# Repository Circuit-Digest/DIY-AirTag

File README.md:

# DIY AirTag: Never Lose Your Keys Again!

We all know that there is nothing more infuriating than forgetting where we placed something important or misplaced things. Losing your keys, wallet, or other valuable items can be a frustrating experience. Apple recognised this common problem and introduced the AirTag, a small, Bluetooth-enabled device that helps you keep track of your belongings. By attaching an AirTag to your items, you can easily locate them using the "Find My" app on your iPhone. The AirTag sends a secure Bluetooth signal that nearby devices in the Find My network can detect, allowing you to see the item's location on a map. Inspired by the functionality and usefulness of Apple's AirTag, we created a DIY solution that brings similar benefits with a personal touch. This project involves creating your own Bluetooth Low Energy (BLE) air tag/key finder that will help you keep your important things safe. The heart of this project is an MDBT50Q-1MV2 BLE  module from Raytac featuring an nRF52840, an ultra low power BLE SoC from Nordic with a 32-bit ARM Cortex-M4 core running at 64MHz. An ADXL345 3-axis accelerometer from Analog devices is also included in the circuit to detect movement. Multiple LEDs and an active buzzer are provided for visual and audible indications. The whole circuit is powered by a 3V CR2032 lithium battery. The key finder function can be used to find the Airtag which the Airtag will output a loud alarm along with LED indications, which makes it easier to find it in both bright and dark environments. With loss prevention mode enabled the Airtag will sound the Alarm and LED indications as soon as the Airtag is disconnected from the smartphone.

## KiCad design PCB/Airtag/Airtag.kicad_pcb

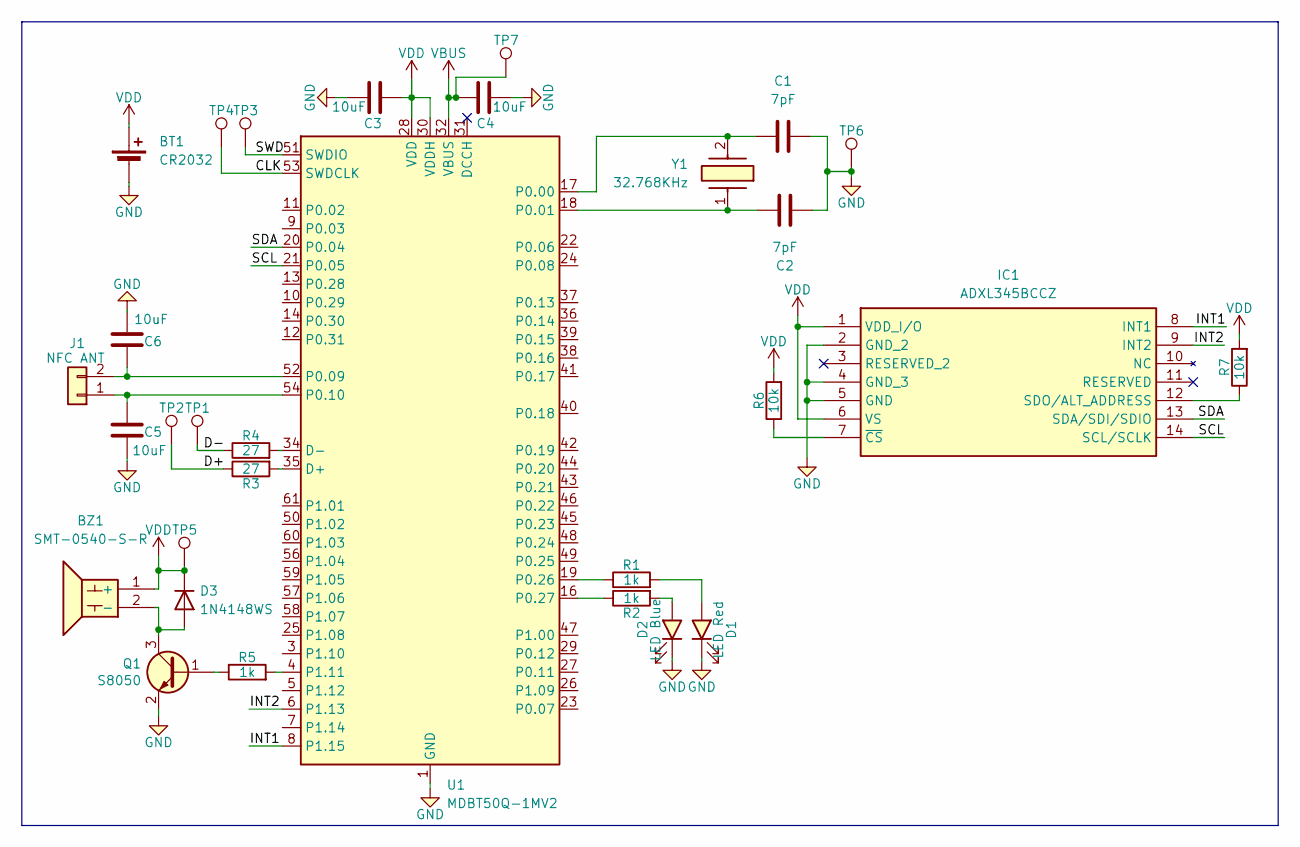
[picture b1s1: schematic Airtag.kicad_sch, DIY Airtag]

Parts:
BT1: CR2032; BH-74B-5; DigiKey Part Number 2057-BH-74B-5-ND
BZ1: SMT-0540-S-R; SMT0540SR; DigiKey Part Number 668-1060-1-ND
C1, C2: 7pF; C_0402_1005Metric; DigiKey Part Number 490-5878-1-ND
C3, C4, C5, C6: 10uF; C_0402_1005Metric; DigiKey Part Number 490-GRM155R60J106ME05DCT-ND
D1: LED Red; LED_0603_1608Metric; DigiKey Part Number 3147-B1911USD-20D000114U1930CT-ND
D2: LED Blue; LED_0603_1608Metric; DigiKey Part Number 3147-B1911NB--20C005314U1930CT-ND
D3: 1N4148WS; D_SOD-323; DigiKey Part Number 4878-1N4148WSCT-ND
IC1: ADXL345BCCZ; LGA14R80P3X6_300X500X100; DigiKey Part Number 505-ADXL345BCCZ-ND
J1: NFC ANT; PinHeader_1x02_P1.27mm_Vertical
Q1: S8050; SOT-23; DigiKey Part Number MMSS8050-L-TPMSCT-ND
R1, R2, R5: 1k; R_0402_1005Metric; DigiKey Part Number P1.00KLCT-ND
R3, R4: 27; R_0402_1005Metric; DigiKey Part Number P27.0LCT-ND
R6, R7: 10k; R_0402_1005Metric; DigiKey Part Number P10.0KLCT-ND
TP1, TP2, TP3, TP4, TP5, TP6, TP7: TestPoint; TestPoint_Pad_D1.0mm
U1: MDBT50Q-1MV2; Raytac_MDBT50Q; DigiKey Part Number 1597-1678-ND
Y1: 32.768KHz; ABS07; DigiKey Part Number 535-9543-1-ND

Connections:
/CLK: TP4.1, U1.53 (SWDCLK)
/D+: R3.1, TP2.1
/D-: R4.1, TP1.1
/INT1: IC1.8 (INT1), U1.8 (P1.15)
/INT2: IC1.9 (INT2), U1.6 (P1.13)
/SCL: IC1.14 (SCL/SCLK), U1.21 (P0.05)
/SDA: IC1.13 (SDA/SDI/SDIO), U1.20 (P0.04)
/SWD: TP3.1, U1.51 (SWDIO)
GND: BT1.2 (-), C1.2, C2.2, C3.1, C4.1, C5.1, C6.2, D1.1 (K), D2.1 (K), IC1.2 (GND_2), IC1.4 (GND_3), IC1.5 (GND), Q1.2 (B), TP6.1, U1.1 (GND), U1.2 (GND), U1.15 (GND), U1.33 (GND), U1.55 (GND)
unnamed: BZ1.2 (-), D3.2 (A), Q1.3 (C)
unnamed: D1.2 (A), R1.2
unnamed: D2.2 (A), R2.2
unnamed: IC1.12 (SDO/ALT_ADDRESS), R7.1
unnamed: IC1.7 (~CS), R6.1
unnamed: C5.2, J1.1, U1.54 (P0.10)
unnamed: C6.1, J1.2, U1.52 (P0.09)
unnamed: Q1.1 (E), R5.1
unnamed: R3.2, U1.35 (D+)
unnamed: R4.2, U1.34 (D-)
unnamed: C1.1, U1.17 (P0.00), Y1.2
unnamed: C2.1, U1.18 (P0.01), Y1.1
unnamed: R1.1, U1.19 (P0.26)
unnamed: R2.1, U1.16 (P0.27)
unnamed: R5.2, U1.4 (P1.11)
VBUS: C4.2, TP7.1, U1.32 (VBUS)
VDD: BT1.1 (+), BZ1.1 (+), C3.2, D3.1 (K), IC1.1 (VDD_I/O), IC1.6 (VS), R6.2, R7.2, TP5.1, U1.28 (VDD), U1.30 (VDDH)

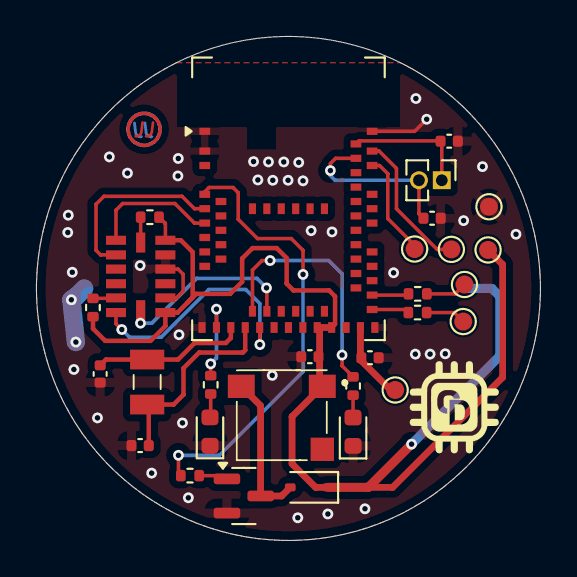
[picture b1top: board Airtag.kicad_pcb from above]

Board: 2 copper layers, 28.0 x 28.0 mm, 30 parts (1 on the bottom side), 26 nets.

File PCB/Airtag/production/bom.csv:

Designator,Footprint,Quantity,Value,LCSC Part #
BT1,BH-74B-5,1,CR2032,
BZ1,SMT0540SR,1,SMT-0540-S-R,
"C1, C2",0402,2,7pF,
"C3, C4, C5, C6",0402,4,10uF,
"D1, D2",0603,2,LED,
D3,D_SOD-323,1,1N4148WS,
IC1,LGA14R80P3X6_300X500X100,1,ADXL345BCCZ,
J1,PinHeader_1x02_P1.27mm_Vertical,1,NFC ANT,
Q1,SOT-23,1,S8050,
"R1, R2, R5",0402,3,1k,
"R3, R4",0402,2,27,
"R6, R7",0402,2,10k,
"TP1, TP2, TP3, TP4, TP5, TP6, TP7",TestPoint_Pad_D1.0mm,7,TestPoint,
U1,Raytac_MDBT50Q,1,MDBT50Q-1MV2,
Y1,ABS07,1,32.768KHz,
